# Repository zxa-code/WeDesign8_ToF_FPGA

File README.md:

# WeDesign8 - 基于FPGA的ToF激光测距数字系统

> 使用京微齐力**HR03PN0U81C7**（STEP-HR03-U81核心板）实现单路ToF激光测距的数据采集、显示、报警与上位机通信。
> 工程包含**FPGA RTL源码与福晞（Fuxi）工程**、**PC上位机（C# WinForms）**、**KiCad电路工程** 与 **可下载位流（ACF）** 四部分。

---

## 一、系统概览

```
       ToF 测距模块 (CN1)
            │  UART 921600 8N1
            ▼
 ┌──────────────────────────── FPGA (top_tof) ────────────────────────────┐
 │  uart_rx ─► tof1_parser(CRC16) ─► 距离 / 强度 / 环境光                  │
 │                │                                                       │
 │                ├─► bcd_conv ─► 2 位数码管 (74HC595)                     │
 │                ├─► disp_chargen + font8x8 ─► 1.12" 128x128 OLED (SPI)  │
 │                │                            └► 0.96" 128x64 OLED (I²C)  │
 │                ├─► alarm_ctrl ─► LED2 报警闪烁 / WS2812 灯效预览        │
 │                └─► 文本行组帧 ─► uart_tx ─► 上位机 (SDAM_Host_V2)       │
 │  输入：4 键 + 旋转编码器 + 拨码 SW0..3 + KEY_A/KEY_B                    │
 └─────────────────────────────────────────────────────────────────────────┘
```

- **主控**：HR03PN0U81C7，12MHz板载时钟，单时钟域设计。
- **数据链路**：ToF模块 → FPGA固定 **921600** 波特率；FPGA → PC的调试串口速率由拨码选择（9600 / 115200 / 230400 / 921600）。
- **本地显示**：SPI 128×128 OLED（SH1107）+ I²C 128×64 OLED（SSD1306）+ 2 位数码管。
- **交互**：板载4键、旋转编码器、扩展板KEY_A/KEY_B，可设置报警阈值、灯效与查看信息页。
- **报警**：距离低于阈值时LED2以2Hz闪烁；WS2812仅在设置页手动预览灯效。

---

## 二、目录结构

```
WeDesign8_ToF_FPGA/
├─ 01_fuxi projects/        FPGA 工程（Fuxi 2025.1）
│  ├─ top_tof.v             顶层：链路、串口、显示、LED、命令重发
│  ├─ tof1_parser.v         SDAM 帧解析 + CRC16 校验（自动重同步）
│  ├─ crc16_modbus.v        CRC16/Modbus 单字节递推（组合逻辑）
│  ├─ uart_rx.v / uart_tx.v 8N1 串口，8 倍过采样 / 累加器分频
│  ├─ bcd_conv.v            double-dabble 二进制→5 位 BCD
│  ├─ disp_chargen.v        46 行 × 16 列文本内容（纯组合）
│  ├─ font8x8.v             5×7 点阵字库（按列输出）
│  ├─ oled_sh1107.v         128×128 SPI OLED 驱动
│  ├─ oled_ssd1306.v        128×64 I²C OLED 驱动（共享字库）
│  ├─ seg7_595.v            2 位共阴数码管 + 74HC595 扫描
│  ├─ key_scan.v            5 通道 20 ms 消抖
│  ├─ rotary_enc.v          旋转编码器正交解码
│  ├─ ui_ctrl.v             单页菜单：ALARM / WARN DIST / LIGHT STYLE / INFO
│  ├─ alarm_ctrl.v          阈值报警 + 6 种灯效
│  ├─ ws2812_drv.v          两颗级联 WS2812 驱动
│  ├─ project.lpf           引脚约束（LPF）与 IO 电平
│  ├─ top_tof.aoc           Fuxi 工程 IO 约束
│  ├─ fuxi_run.sh           综合→布局布线→STA→位流生成流程
│  ├─ scripts/              cstool / cstimer 各阶段 TCL 脚本
│  └─ outputs/              综合、布局布线、STA 报告与网表
├─ 02_hostcpt_src/          PC 上位机（C# / .NET Framework 4.8）
│  ├─ exe/SDAM_Host_V2.exe  可直接运行
│  └─ src/                  源码、构建脚本、协议单元测试
├─ 03_Circuit/              KiCad 10 电路工程（由嘉立创 EDA 导入）
│  └─ kicanvas_fix/         网页端 KiCanvas 网络缺失修复脚本与上传包
└─ 04_downloadable acf/     生成的下载位流 top_tof_bin.acf
```

---

## 三、FPGA 设计要点

### 1. 复位策略
HR02/HR03内部配置寄存器上电默认输出为 1，单计数器POR可能上电首拍即判完成。顶层采用 **升计数饱和 + 降计数归零** 双计数器（`por_up` / `por_dn`），保证无论初值如何都得到约 **5.46 ms** 的确定性复位窗口；`KEY_B` 可随时拉低复位。

### 2. ToF 通信与帧格式
- 上电复位后先**等待约1.4s**，再发送一条9字节启动流命令：

  ```
  A5 03 20 01 00 00 00 02 6E
  ```

- 一次“尝试”只发这一帧，随后静默1.4s等待模块推流；未锁定则按1.4s周期重发，`KEY_A` 可立即补发，收到合法帧后停止打扰。
- 上行帧格式：

  ```
  A5 03 20 CMD RSV LEN_H LEN_L + 14 B data + CRC_H CRC_L
  ```

  data 为小端：主目标距离（mm）、主目标强度、环境光。CRC为**CRC16/Modbus**（初值0xFFFF、反射、poly 0xA001），同时兼容高低字节交换的写法。
- 解析器支持帧头重同步，任意字节丢失后可自动恢复。

### 3. 本地显示
| 外设 | 接口 | 说明 |
| --- | --- | --- |
| 1.12" 128×128 OLED | 4 线 SPI（3 MHz，CS 接地） | 16行 × 16字符，显示距离/强度/环境光/计数/链路/命令次数等 |
| 0.96" 128×64 OLED | I²C（0x3C，SCL=IO31，SDA=IO32 开漏） | 单页菜单 + 3 个子页，与小屏共享 `disp_chargen` 和 `font8x8` |
| 2 位数码管 | 74HC595 串行 | 按 `<1 m` 显示厘米、`1~9.99 m` 显示米.分米、`≥10 m` 显示十米/米 |

两块 OLED 共享一份字库与字符源，顶层在 SPI 屏 `S_LOAD` 拍仲裁，节省 LUT。

### 4. 交互与报警
- `key_scan`：1 kHz 采样、20 ms 消抖；`rotary_enc`：4 状态正交解码，每档一个 step。
- `ui_ctrl`：主页 4 项（ALARM 开关 / WARN DIST / LIGHT STYLE / INFO），旋转选择、按键确认；WARN 阈值 0.10–20.00 m，精度 0.01 m（BCD `{十米,米,分米,厘米}` 避免除法），默认 5.00 m。
- `alarm_ctrl`：判据 `alarm_en && link_ok && 距离有效且 ≤ alarm_mm`，带 200 ms 超阈值清除与 1 s 失链清除；报警由 **LED2 2 Hz 闪烁** 指示。6 种灯效（红闪 / 黄闪 / 绿常亮 / 警灯 / 呼吸 / 彩虹）仅在 LIGHT STYLE 子页预览。

### 5. LED 与拨码语义
| 拨码 | 含义 |
| --- | --- |
| 恰好 1 个 ON | 打开上位机串口：SW0=9600，SW1=115200，SW2=230400，SW3=921600 |
| 0 个 ON | 关闭上位机串口，OLED 显示 `OFF` |
| 多个 ON | 非法，串口关闭，OLED 显示 `ERROR` |

拨码只影响 **FPGA→PC** 的调试串口；ToF 侧固定 921600，测距、OLED、数码管不受影响。

LED（核心板低电平点亮，代码中统一取反）：
`LED1` 心跳 / `LED2` 距离报警 2 Hz / `LED3` 链路 OK / `LED4` 上位机串口已开 / `LED5..8` 四档位指示。

### 6. 资源占用（Fuxi 2025.1，2026-11-14 综合）
- 综合状态：**Successful**，0 error / 6 warning。
- 寄存器 1164 / 2048，IO 37 / 66，未使用 EMB 与 PLL。
- 布局布线、时序分析（agtc 85 ℃ / 0.81 V）与位流生成均已跑通，产物见 `outputs/` 与 `04_downloadable acf/`。

---

## 四、上位机（SDAM Host V2）

- 语言/框架：C# WinForms，.NET Framework 4.8（Windows 10/11 自带，无需额外安装）。
- **纯接收设计**：只解析 FPGA 上行的 ASCII 文本行，不向串口写任何字节。
- 数据格式（约 49 B，`\r\n` 结尾）：

  ```
  D=0843 I=0924 A=0012 C=00 F=0000 U=3 B=0000 L=1
  ```

  | 字段 | 含义 |
  | --- | --- |
  | `D=` | 主目标距离，1 mm/LSB（4 位十六进制） |
  | `I=` | 回波强度（4 位十六进制） |
  | `A=` | 环境光基底（4 位十六进制） |
  | `C=` | CRC 错误帧计数（2 位十六进制） |
  | `F=` | 合法帧计数（4 位十六进制） |
  | `U=` | 上位机串口档位 0..3 |
  | `B=` | 累计接收字节数 mod 65536（4 位十六进制） |
  | `L=` | 链路状态（1=1.4 s 内有合法帧） |

- 功能：三路实时曲线（10/30/60/300 s）、链路统计、日志、CSV 导出、曲线 PNG 导出。
- 构建与测试：
  ```bat
  cd 02_hostcpt_src\src
  build.bat            :: 使用系统自带 csc.exe，无需 VS
  cd tests
  run_tests.bat        :: 协议解析单元测试，77 项断言
  ```

---

## 五、电路工程

- `03_Circuit/` 为 KiCad 10 工程（由嘉立创 EDA 专业版导入），含原理图、PCB、封装库与符号库。
- 电子森林网页端使用旧版 KiCanvas 解析器，无法识别 KiCad 10 的“仅网络名”格式，且 polygon 内嵌 `arc` 会导致白屏。`kicanvas_fix/convert_kicad10_to_kicanvas.py` 会：
  1. 将 `(arc ...)` 按 12° 采样展开为折线；
  2. 插入顶层网络表并把 pad/segment/via/zone 的 net 引用改为旧格式。
- 修复后：KiCad 10 可正常打开（47 nets / 219 tracks），网页端 Nets 面板可显示 47 个网络并高亮走线。
- 上传包：`03_Circuit/kicanvas_fix/WeDesign8_ToF_FPGA_kicanvas_upload.zip`。
- **注意**：不要用 KiCad 10 打开修复版再保存，否则会写回新格式；改板请修改原工程后重新转换。

---

## 六、复现与下载

1. 用福晞（Fuxi 2025.1）打开 `01_fuxi projects/top_tof.hpr`（或对应工程），综合→布局布线→生成位流；
   也可按 `fuxi_run.sh` 依次调用 `cstool` / `agtc` / `cstimer` / `abcgen` / `acfgen`。
2. 位流输出为 `04_downloadable acf/top_tof_bin.acf`，使用官方下载工具烧录至 HR03PN0U81C7。
3. 按原理图连接 ToF 模块（CN1）、两块 OLED、数码管与 WS2812，上电后约 0.7 s 全亮自检，随后正常显示。
4. PC端运行`02_hostcpt_src/exe/SDAM_Host_V2.exe`，选择串口与拨码对应的波特率即可接收。

---

## 七、版本说明

顶层当前版本为**V3.0-P4.1**（2026-11-14）。近几次主要迭代：

- **V2.0**：拨码语义由“ToF速率”改为“上位机串口速率”，ToF固定921600的通信波特率；LED改正逻辑；放弃第二路ToF。
- **V3.0-P1~P2**：新增4个板载可交互按键、旋转编码器与I²C 128×64 OLED 驱动。
- **V3.0-P3~P3d**：加入菜单/子页UI，两屏共享一份字库与字符源以节省LUT。
- **V3.0-P4~P4.1**：距离报警（ALARM / WARN DIST）与 6 种 WS2812 灯效；报警改由 LED2 指示，WS2812 仅手动预览。

---

## 八、说明

- 本工程为综合课程设计项目，代码中保留了较详细的中文注释与版本修订记录，便于继续维护。
- 各模块的设计背景、调试过程中遇到的问题及取舍，详见源码文件头注释。

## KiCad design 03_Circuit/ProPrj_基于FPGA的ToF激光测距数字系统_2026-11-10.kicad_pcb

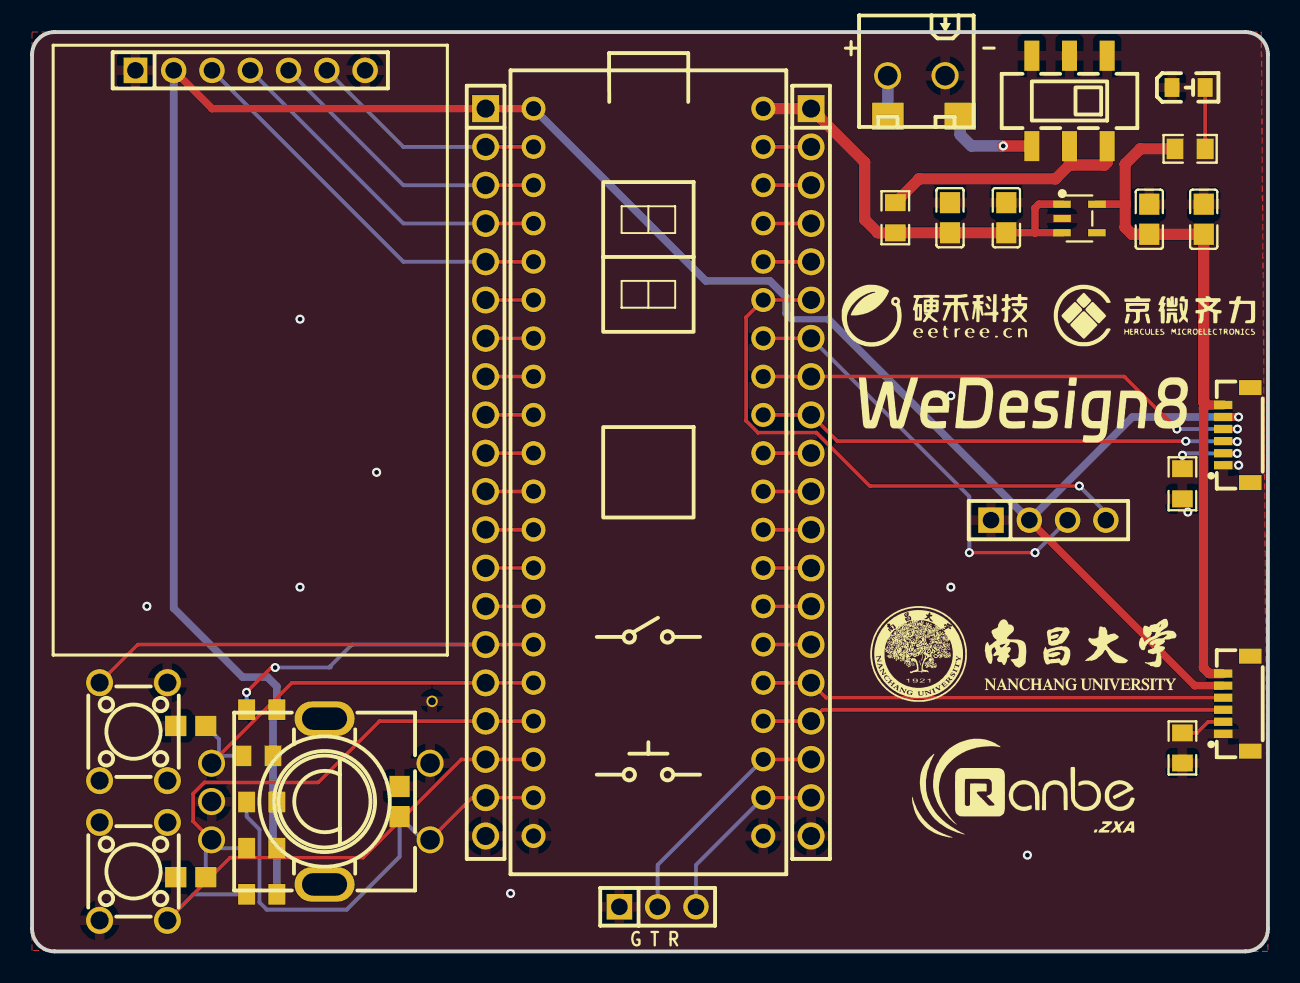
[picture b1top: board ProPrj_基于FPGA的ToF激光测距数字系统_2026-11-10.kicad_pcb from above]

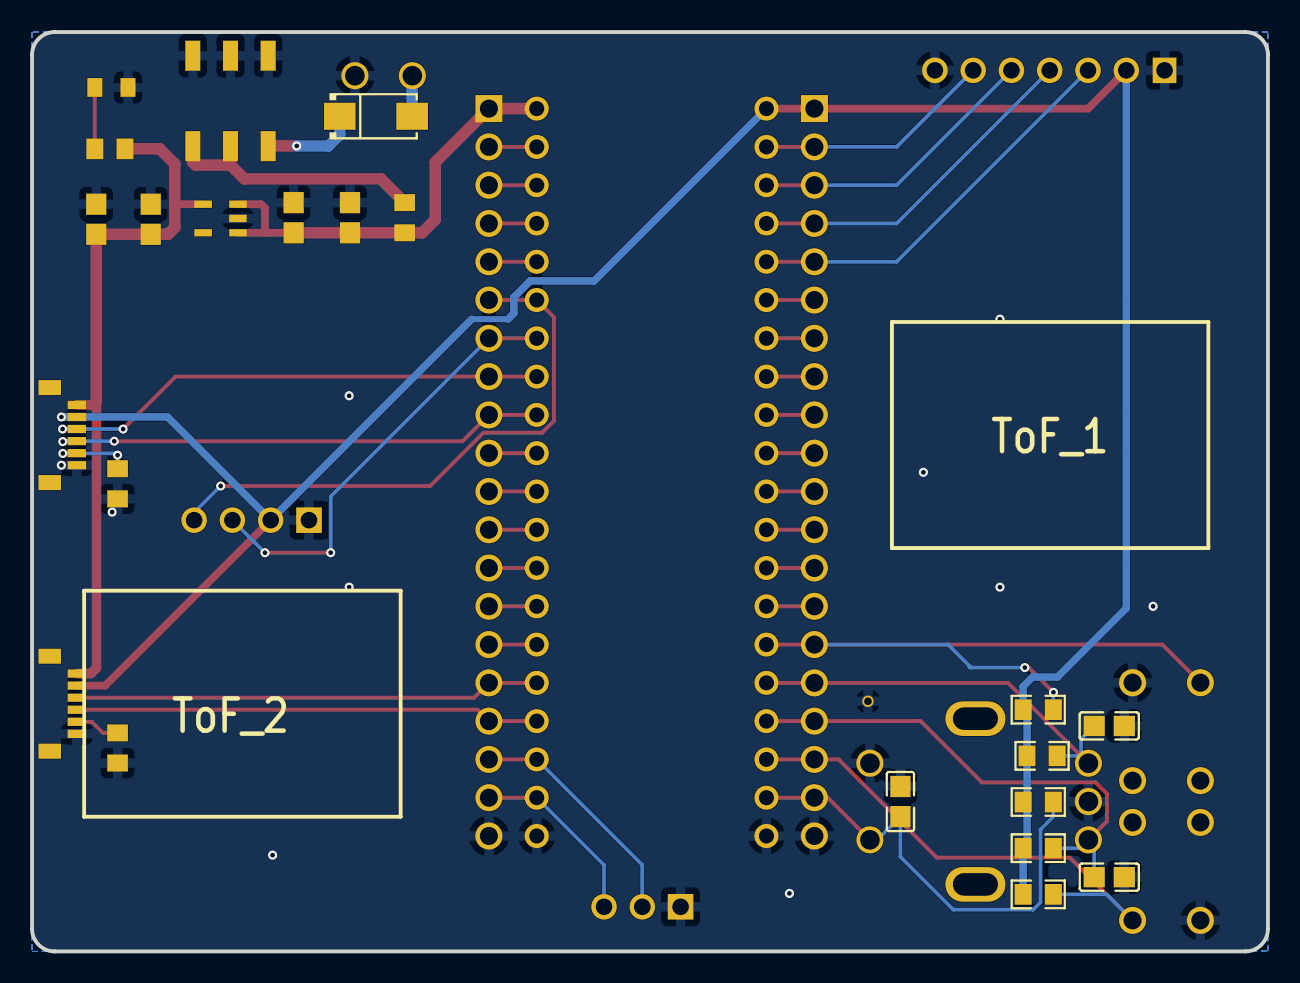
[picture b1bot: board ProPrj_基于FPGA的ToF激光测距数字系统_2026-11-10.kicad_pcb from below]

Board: 2 copper layers, 82.0 x 61.0 mm, 32 parts (9 on the bottom side), 46 nets.

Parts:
C1, C2, C3, C4, C5, C6, C7: C0805
CN1, CN2: CONN-SMD_6P-P0.80_HCTL_HC-0.8-6PWT
DC-5VIN: CONN-TH_2P-P3.81_MX128L-3.81-GN01-02P-CU-Y-A
H1, H2: HDR-TH_20P-P2.54-V-F
KEYA: SW-TH_4P-L6.0-W6.0-P4.50-LS6.5
KEYB: SW-TH_4P-L6.0-W6.0-P4.50-LS6.5
KEYC: 旋转编码器
OFF-ON: SW-SMD_YSSP2AG00
OLED_A: HDR-TH_7P-P2.54-V-F
OLED_B: HDR-TH_4P-P2.54-V-F
PWR-ON: LED_0805
R1, R2, R3, R4, R5, R6, R7, R8: R0805
RO: R0805
U1: STEP-HR03-U81
U2: SMA_L4.2-W2.6-LS5.1-RD
U3: SOT-23-5_L3.0-W1.7-P0.95-LS2.8-BL
UART: HDR-TH_3P-P2.54-V-M

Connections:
3V3: CN1.5, CN2.5, H1.1, OLED_A.2, OLED_B.2, R3.1, R4.1, R5.1, R6.1, R7.1, U1.1
$1N110: DC-5VIN.2, U2.2
$1N112: OFF-ON.3, U2.1
$1N114: OFF-ON.1, OFF-ON.2, RO.1
$1N133: PWR-ON.2, R8.2
DBG_RX: H2.19, U1.22, UART.3
DBG_TX: H2.18, U1.23, UART.2
FPGA_RX1: CN1.4, H2.8, U1.33
FPGA_RX2: CN2.4, H2.16, U1.25
FPGA_TX1: CN1.3, H2.9, U1.32
FPGA_TX2: CN2.3, H2.17, U1.24
GND: C1.2, C2.2, C3.2, C4.1, C5.1, C6.1, C7.1, CN1.1, CN2.1, DC-5VIN.1, H1.20, H2.20, KEYA.1, KEYB.1, KEYC.C, KEYC.D, OFF-ON.4, OFF-ON.5, OFF-ON.6, OLED_A.1, OLED_A.7, OLED_B.1, PWR-ON.1, R1.2, R2.2, U1.20, U1.21, U3.2, UART.1
GPIO1: CN1.2, R1.1
GPIO2: CN2.2, R2.1
I2C_SCL: H2.7, OLED_B.3, U1.34
I2C_SDA: H2.6, OLED_B.4, U1.35
IO5: H1.6, U1.6
IO6: H1.7, U1.7
IO7: H1.8, U1.8
IO8: H1.9, U1.9
IO9: H1.10, U1.10
IO10: H1.11, U1.11
IO11: H1.12, U1.12
IO12: H1.13, U1.13
IO13: H1.14, U1.14
IO23: H2.15, U1.26
IO24: H2.14, U1.27
IO25: H2.13, U1.28
IO26: H2.12, U1.29
IO27: H2.11, U1.30
IO28: H2.10, U1.31
IO33: H2.5, U1.36
IO34: H2.4, U1.37
IO35: H2.3, U1.38
IO36: H2.2, U1.39
KEY_A: H1.18, KEYA.3, R3.2, U1.18
KEY_B: H1.15, KEYB.3, R4.2, U1.15
KEY_ENC: C2.1, H1.19, KEYC.E, R6.2, U1.19
LASER+3V3: C6.2, C7.2, CN1.6, CN2.6, R8.1, U3.5
OLED_DC: H1.2, OLED_A.6, U1.2
OLED_RES: H1.3, OLED_A.5, U1.3
PHASE_A: C3.1, H1.16, KEYC.A, R5.2, U1.16
PHASE_B: C1.1, H1.17, KEYC.B, R7.2, U1.17
SPI_SCL: H1.5, OLED_A.3, U1.5
SPI_SDA: H1.4, OLED_A.4, U1.4
VCC+5V: C4.2, C5.2, H2.1, RO.2, U1.40, U3.1, U3.3
